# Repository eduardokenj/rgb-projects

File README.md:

Aqui nesse repositorio você encontrará os projeots relacionados ao RGB, como switchs para EURO SCART, bypass e adaptadores.
Caso queira produzir a placa recomendo esses dois sites abaixo ambos no exterior, mas que enviam para o Brasil

 SEEED FUSION: https://www.seeedstudio.com/fusion_pcb.html (envie o arquivo .zip incluso no diretorio do projeto);
	
 OSH PARK: https://oshpark.com/ (envie o arquivo .brd que se encontra no dietorio do projeto).
	
E boa parte dos compoenentes são encontrados já nacionalizados.

Os projetos nesse repositorio git são open hardware e feitos para a comunidade.

Caso queira doar via paypal só mandar o pagameto para eduardokenj@gmail.com
Ou via PicPay picpay.me/eduardo.asakura

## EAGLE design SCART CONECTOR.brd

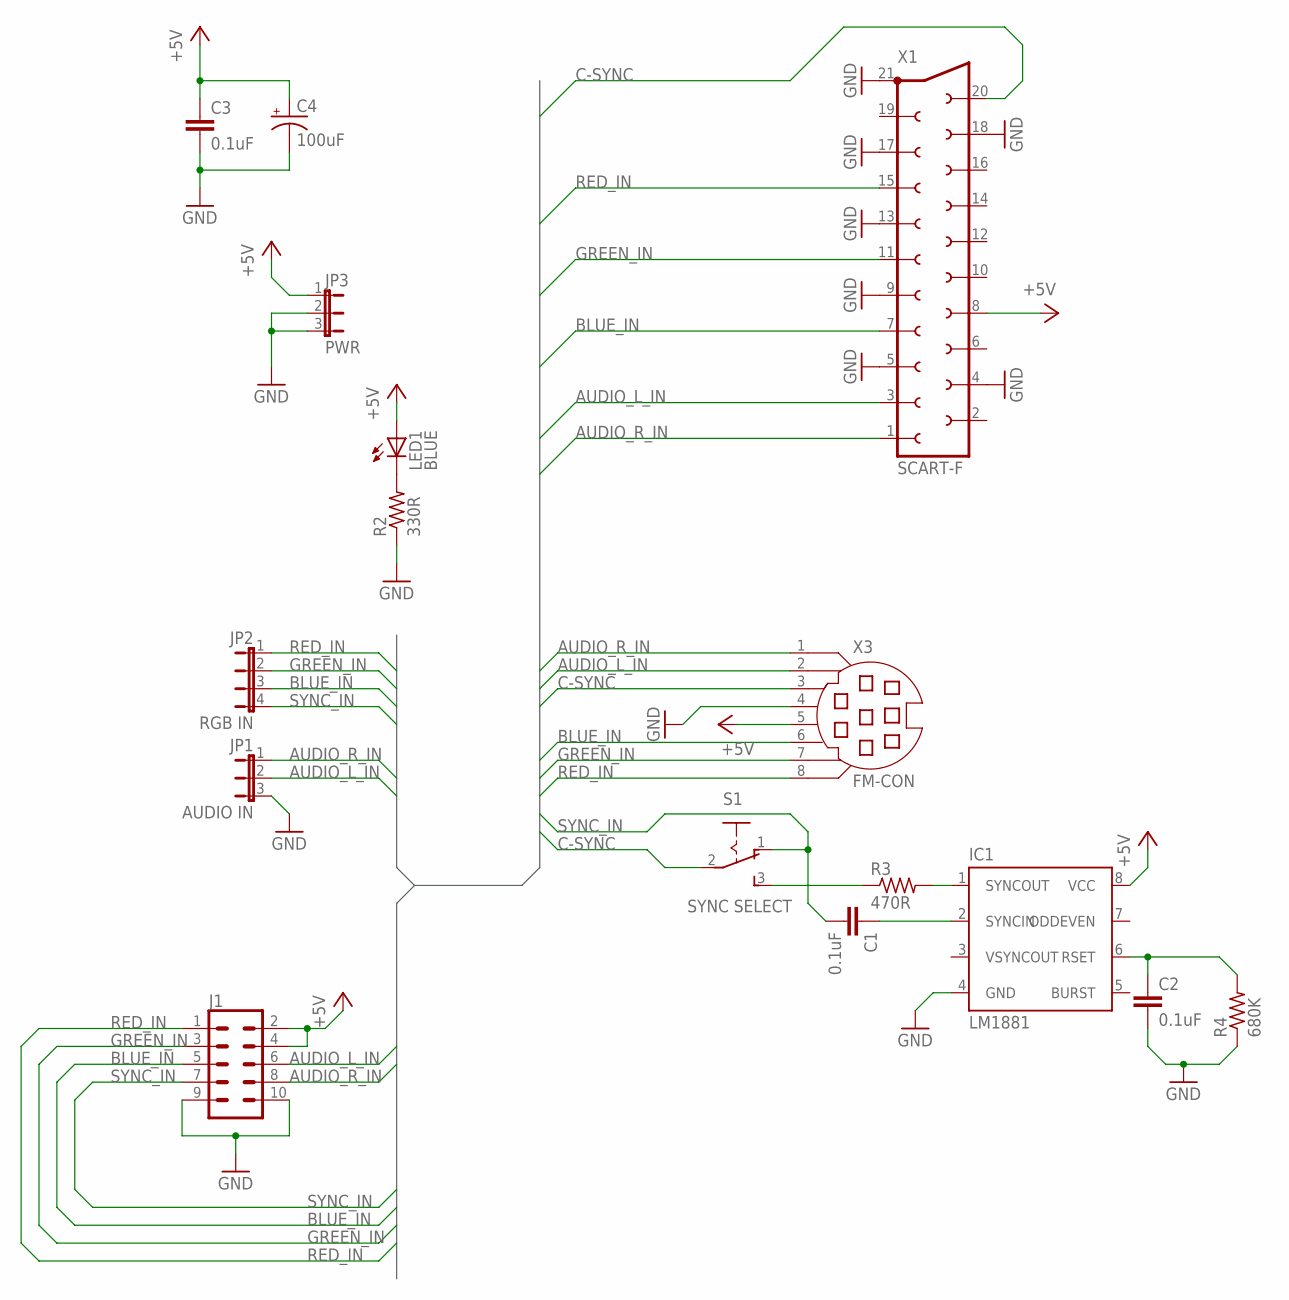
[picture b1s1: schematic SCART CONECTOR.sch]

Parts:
C1, C2, C3: 0.1uF; C7.5B3
C4: 100uF; E5-13
IC1: LM1881; DIL08
J1: CONN_05X2SHD-NS; 2X5-SHROUDED-NS
JP1: AUDIO IN; JP2
JP2: RGB IN; JP4
JP3: PWR; JP2
LED1: BLUE; LED5MM
R2: 330R; 0204/7
R3: 470R; 0204/7
R4: 680K; 0204/7
S1: SYNC SELECT; 255SB
X1: SCART-F
X3: FM-CON; MDIN08SS

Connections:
+5V: C3.1, C4.+, IC1.8 (VCC), J1.2, J1.4, JP3.1, LED1.A, X1.8, X3.5
AUDIO_L_IN: J1.6, JP1.2, X1.3, X3.2
AUDIO_R_IN: J1.8, JP1.1, X1.1, X3.1
BLUE_IN: J1.5, JP2.3, X1.7, X3.6
C-SYNC: S1.2, X1.20, X3.3
GND: C2.2, C3.2, C4.-, IC1.4 (GND), J1.9, J1.10, JP1.3, JP3.2, JP3.3, R2.1, R4.1, X1.4, X1.5, X1.9, X1.13, X1.17, X1.18, X1.21, X3.4
GREEN_IN: J1.3, JP2.2, X1.11, X3.7
unnamed: R3.1, S1.3 (S)
unnamed: IC1.1 (SYNCOUT), R3.2
unnamed: LED1.K (C), R2.2
unnamed: C1.1, IC1.2 (SYNCIN)
unnamed: C2.1, IC1.6 (RSET), R4.2
RED_IN: J1.1, JP2.1, X1.15, X3.8
SYNC_IN: C1.2, J1.7, JP2.4, S1.1 (O)

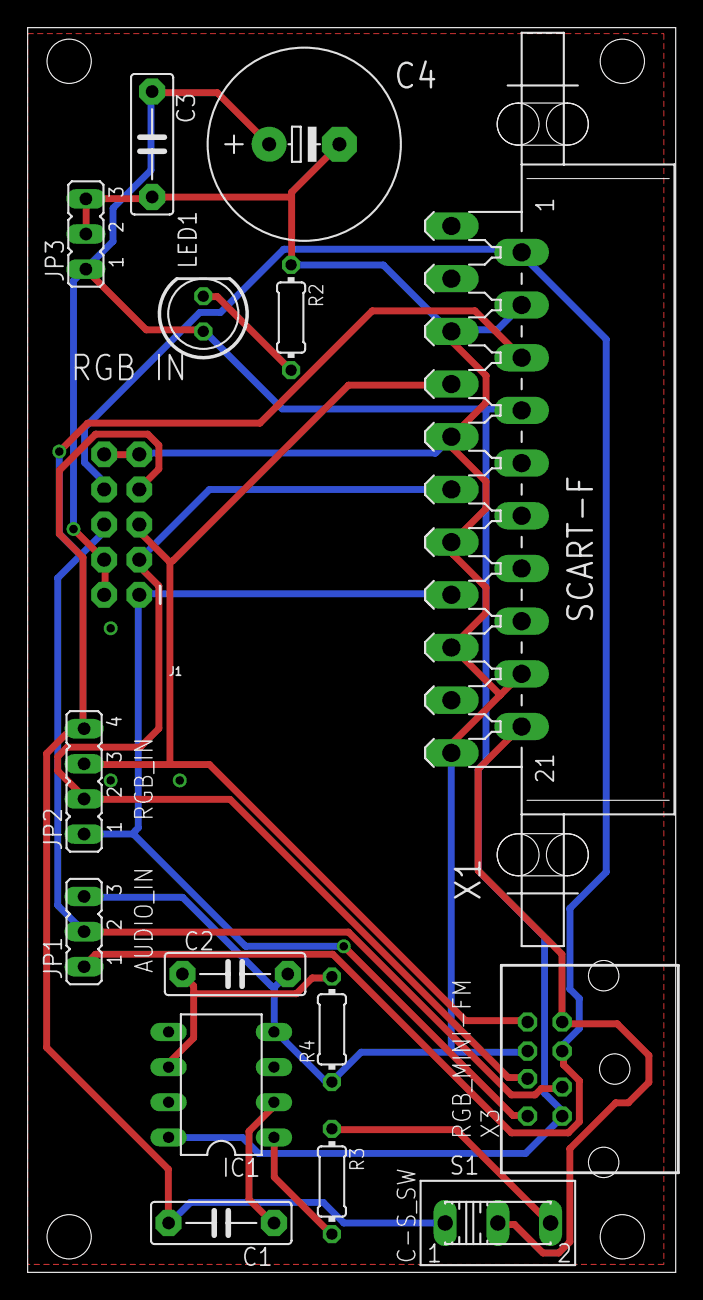
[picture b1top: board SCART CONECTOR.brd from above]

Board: 2 copper layers, 46.9 x 90.0 mm, 16 parts (0 on the bottom side), 14 nets.

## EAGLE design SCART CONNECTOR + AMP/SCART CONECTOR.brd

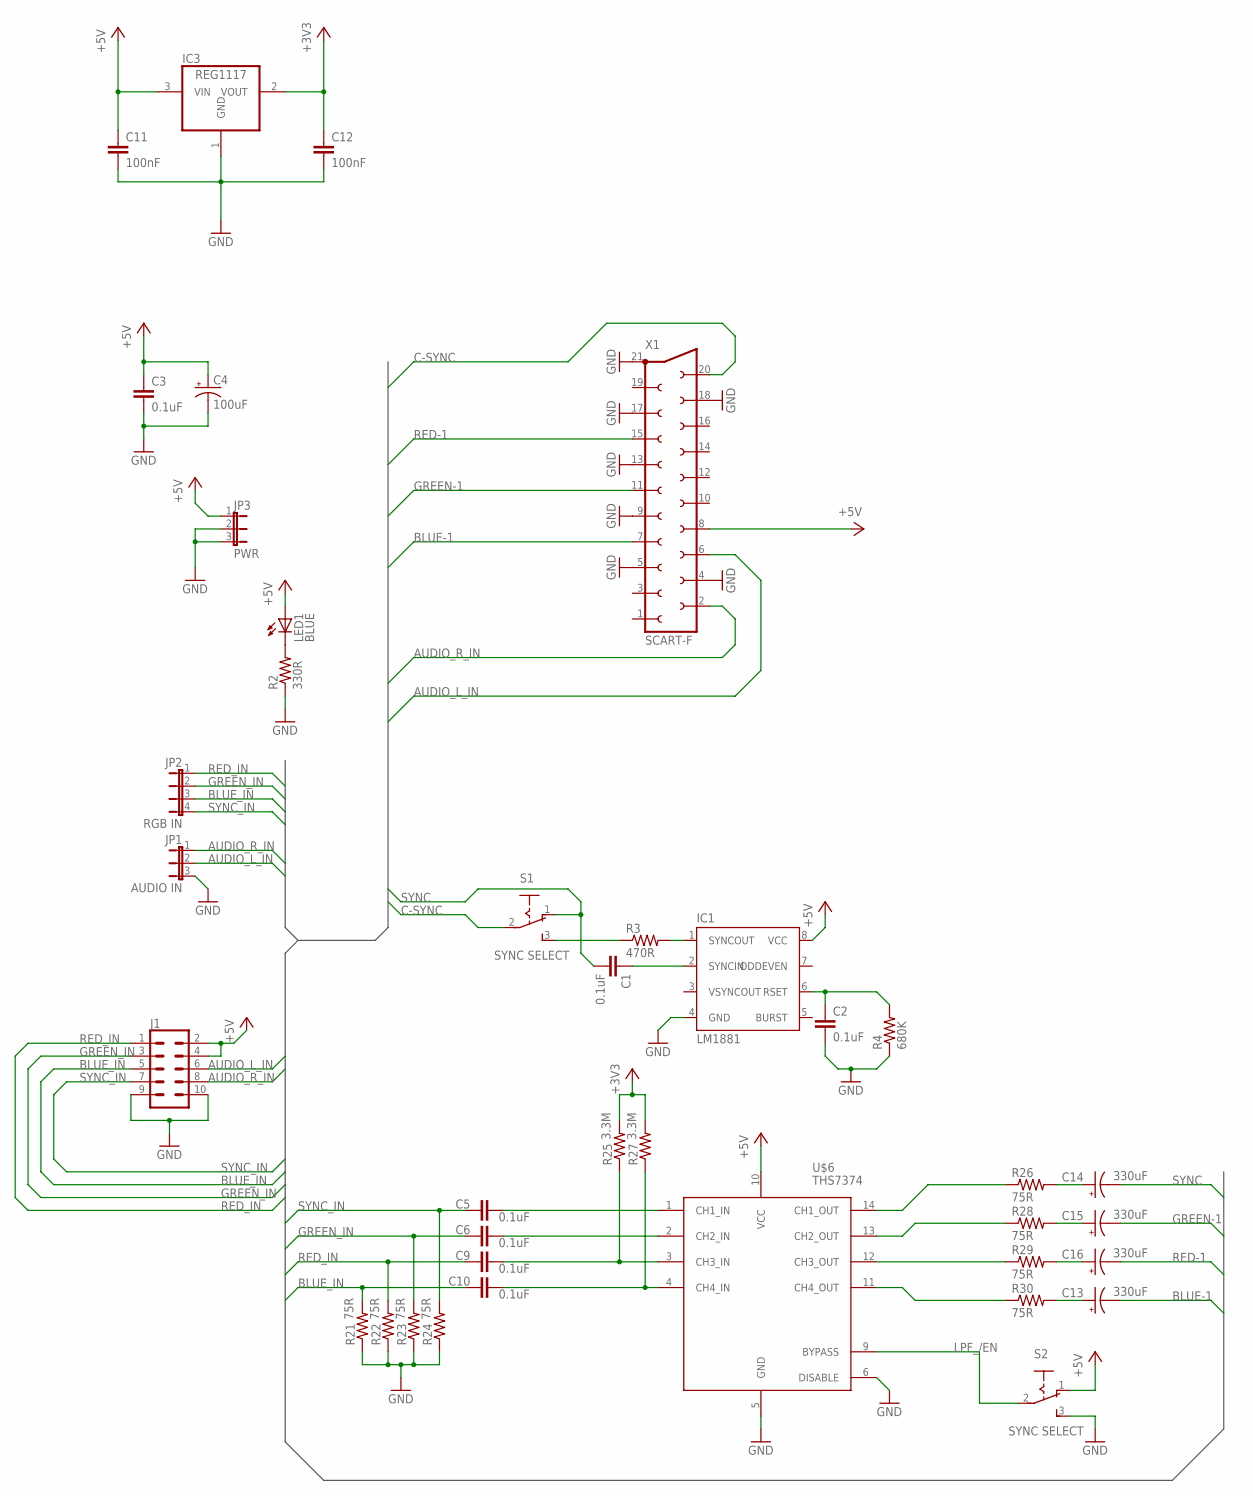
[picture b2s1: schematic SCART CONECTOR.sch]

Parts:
C1, C2, C3: 0.1uF; C7.5B3
C4: 100uF; E5-13
C5, C6, C9, C10: 0.1uF; C050-025X075
C11, C12: 100nF; C075-032X103
C13, C14, C15, C16: 330uF; D/7343-31W
IC1: LM1881; DIL08
IC3: REG1117; SOT223
J1: CONN_05X2SHD-NS; 2X5-SHROUDED-NS
JP1: AUDIO IN; JP2
JP2: RGB IN; JP4
JP3: PWR; JP2
LED1: BLUE; LED5MM
R2: 330R; 0204/7
R3: 470R; 0204/7
R4: 680K; 0204/7
R21, R22, R23, R24: 75R; 0204V
R25, R27: 3.3M; 0204/7
R26, R28, R29, R30: 75R; 0204/7
S1, S2: SYNC SELECT; 255SB
U$6: THS7374; TSSOP-14
X1: SCART-F

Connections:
+3V3: C12.1, IC3.2 (VOUT), R25.2, R27.2
+5V: C3.1, C4.+, C11.1, IC1.8 (VCC), IC3.3 (VIN), J1.2, J1.4, JP3.1, LED1.A, S2.1 (O), U$6.10 (VCC), X1.8
AUDIO_L_IN: J1.6, JP1.2, X1.6
AUDIO_R_IN: J1.8, JP1.1, X1.2
BLUE-1: C13.-, X1.7
BLUE_IN: C10.1, J1.5, JP2.3, R21.2
C-SYNC: S1.2, X1.20
GND: C2.2, C3.2, C4.-, C11.2, C12.2, IC1.4 (GND), IC3.1 (GND), J1.9, J1.10, JP1.3, JP3.2, JP3.3, R2.1, R4.1, R21.1, R22.1, R23.1, R24.1, S2.3 (S), U$6.5 (GND), U$6.6 (DISABLE), X1.4, X1.5, X1.9, X1.13, X1.17, X1.18, X1.21
GREEN-1: C15.-, X1.11
GREEN_IN: C6.1, J1.3, JP2.2, R23.2
LPF_/EN: S2.2, U$6.9 (BYPASS)
unnamed: R3.1, S1.3 (S)
unnamed: IC1.1 (SYNCOUT), R3.2
unnamed: LED1.K (C), R2.2
unnamed: C1.1, IC1.2 (SYNCIN)
unnamed: C2.1, IC1.6 (RSET), R4.2
unnamed: C6.2, U$6.2 (CH2_IN)
unnamed: C9.2, R25.1, U$6.3 (CH3_IN)
unnamed: C10.2, R27.1, U$6.4 (CH4_IN)
unnamed: C5.2, U$6.1 (CH1_IN)
unnamed: R26.1, U$6.14 (CH1_OUT)
unnamed: R28.1, U$6.13 (CH2_OUT)
unnamed: R29.1, U$6.12 (CH3_OUT)
unnamed: R30.1, U$6.11 (CH4_OUT)
unnamed: C13.+, R30.2
unnamed: C16.+, R29.2
unnamed: C15.+, R28.2
unnamed: C14.+, R26.2
RED-1: C16.-, X1.15
RED_IN: C9.1, J1.1, JP2.1, R22.2
SYNC: C1.2, C14.-, S1.1 (O)
SYNC_IN: C5.1, J1.7, JP2.4, R24.2

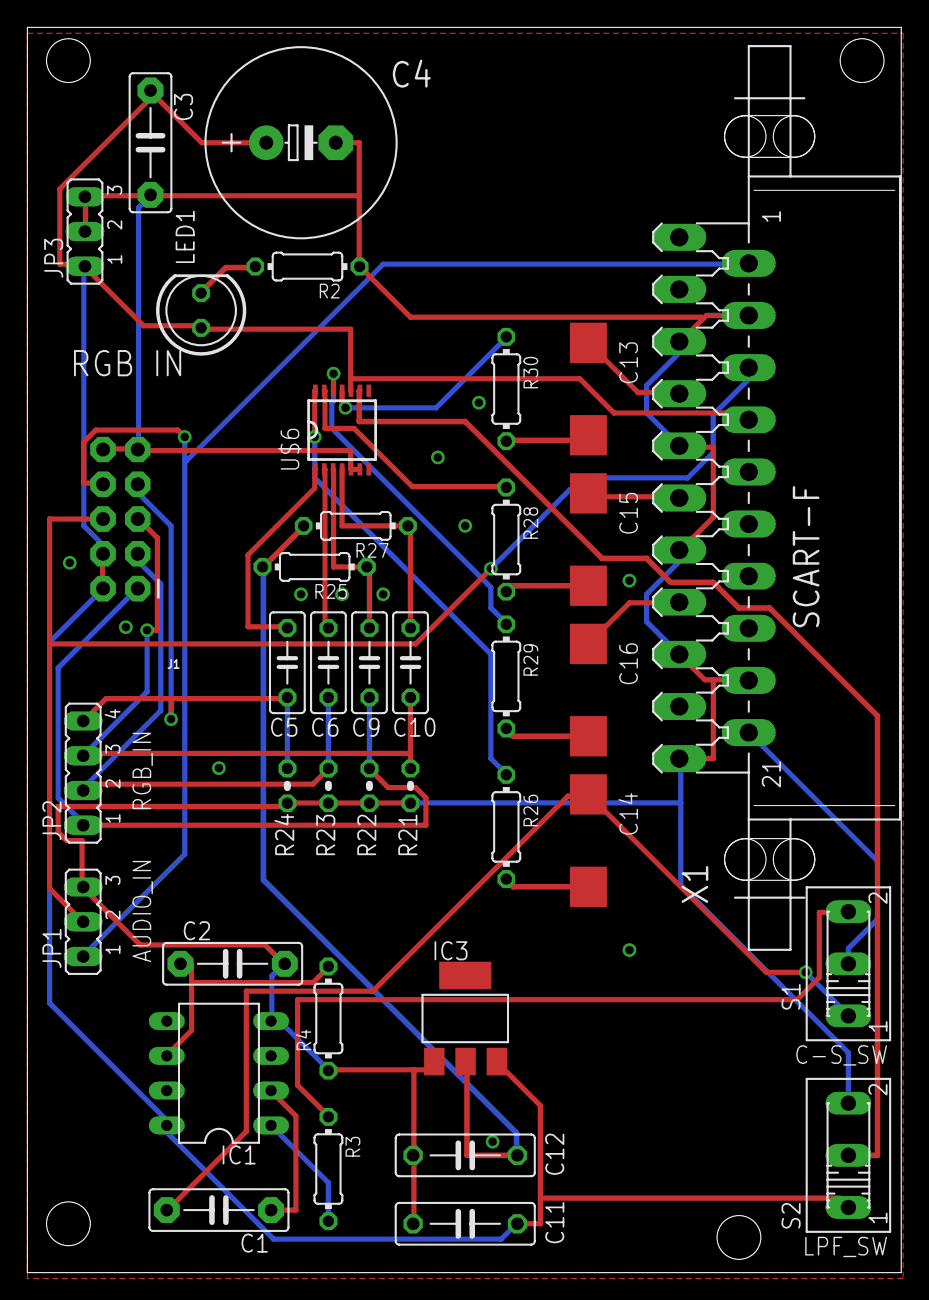
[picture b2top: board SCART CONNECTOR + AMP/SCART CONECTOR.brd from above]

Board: 2 copper layers, 63.9 x 91.0 mm, 38 parts (0 on the bottom side), 32 nets.

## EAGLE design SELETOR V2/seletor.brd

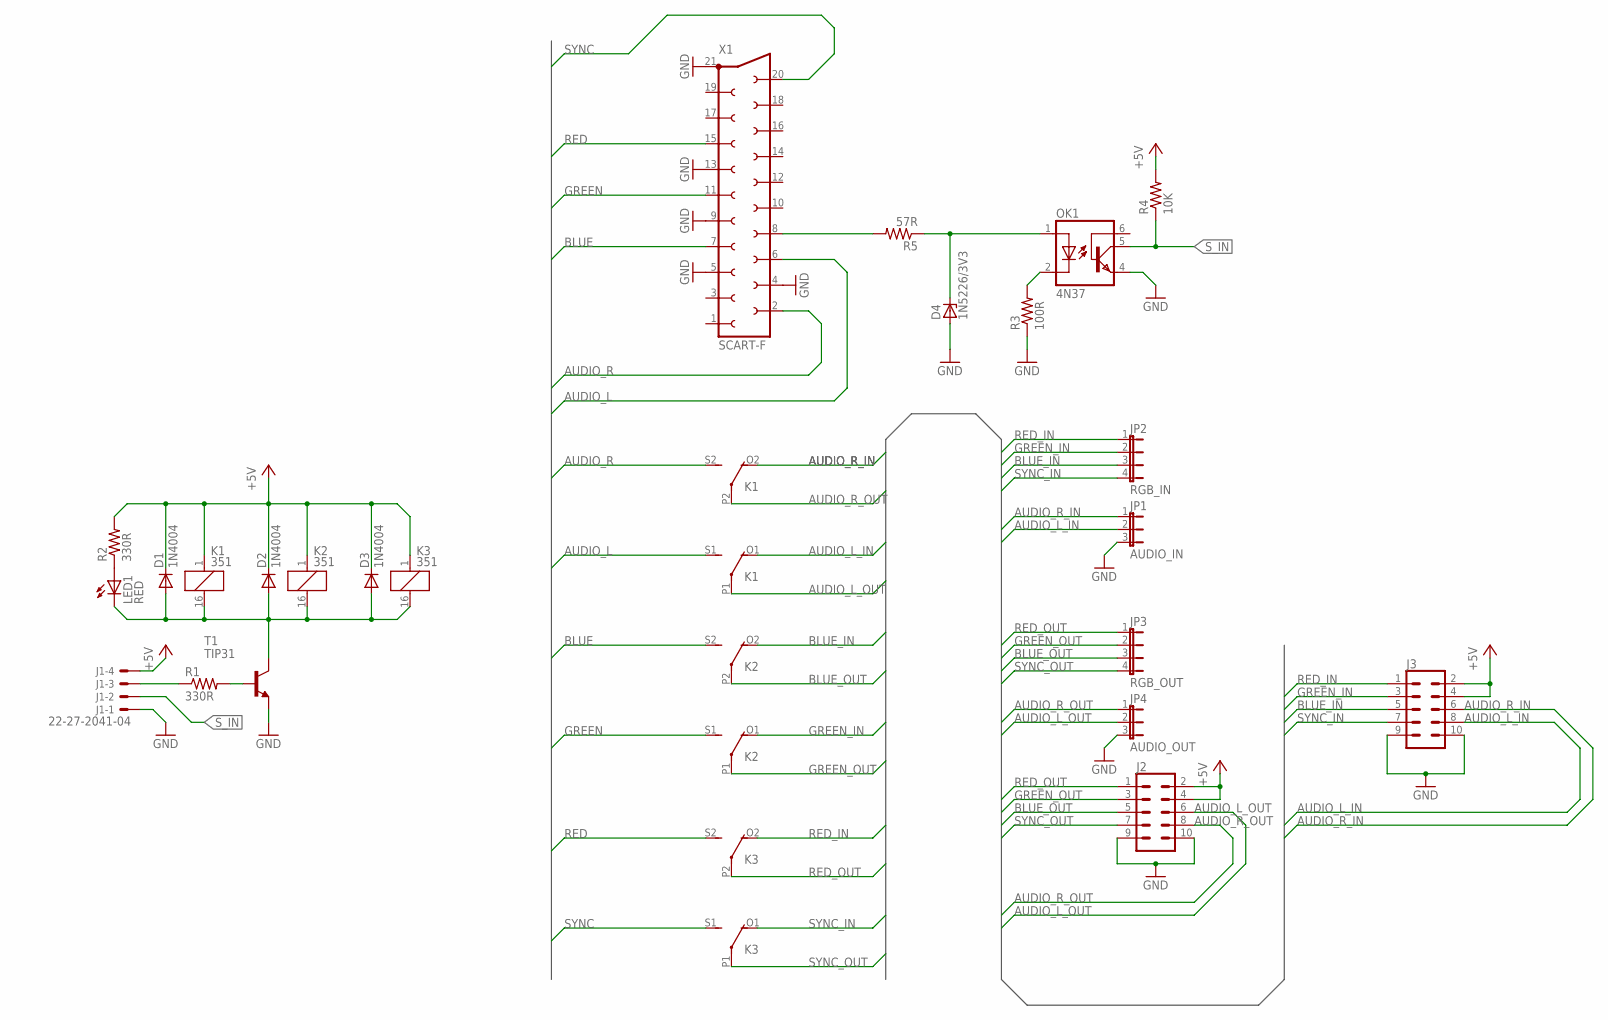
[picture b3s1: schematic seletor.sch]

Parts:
D1, D2, D3: 1N4004; DO41-10
D4: 1N5226/3V3; DO34Z7
J1: 22-27-2041-04; 6410-04
J2, J3: CONN_05X2SHD-NS; 2X5-SHROUDED-NS
JP1: AUDIO_IN; JP2
JP2: RGB_IN; JP4
JP3: RGB_OUT; JP4
JP4: AUDIO_OUT; JP2
K1, K2, K3: 351
LED1: RED; LED5MM
OK1: 4N37; DIL06
R1, R2: 330R; 0204/7
R3: 100R; 0204/7
R4: 10K; 0204/7
R5: 57R; 0204/7
T1: TIP31; TO220
X1: SCART-F

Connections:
+5V: D1.C, D2.C, D3.C, J1.4, J2.2, J2.4, J3.2, J3.4, K1.1, K2.1, K3.1, R2.2, R4.2
AUDIO_L: K1.S1 (S), X1.6
AUDIO_L_IN: J3.8, JP1.2, K1.O1 (O)
AUDIO_L_OUT: J2.6, JP4.2, K1.P1
AUDIO_R: K1.S2 (S), X1.2
AUDIO_R_IN: J3.6, JP1.1, K1.O2 (O)
AUDIO_R_OUT: J2.8, JP4.1, K1.P2
BLUE: K2.S2 (S), X1.7
BLUE_IN: J3.5, JP2.3, K2.O2 (O)
BLUE_OUT: J2.5, JP3.3, K2.P2
GND: D4.A, J1.1, J2.9, J2.10, J3.9, J3.10, JP1.3, JP4.3, OK1.4 (EMI), R3.1, T1.3 (E), X1.4, X1.5, X1.9, X1.13, X1.21
GREEN: K2.S1 (S), X1.11
GREEN_IN: J3.3, JP2.2, K2.O1 (O)
GREEN_OUT: J2.3, JP3.2, K2.P1
unnamed: J1.3, R1.1
unnamed: D1.A, D2.A, D3.A, K1.16 (2), K2.16 (2), K3.16 (2), LED1.K (C), T1.2 (C)
unnamed: LED1.A, R2.1
unnamed: D4.C, OK1.1 (A), R5.1
unnamed: OK1.2 (C), R3.2
unnamed: R5.2, X1.8
unnamed: R1.2, T1.1 (B)
RED: K3.S2 (S), X1.15
RED_IN: J3.1, JP2.1, K3.O2 (O)
RED_OUT: J2.1, JP3.1, K3.P2
SYNC: K3.S1 (S), X1.20
SYNC_IN: J3.7, JP2.4, K3.O1 (O)
SYNC_OUT: J2.7, JP3.4, K3.P1
S_IN: J1.2, OK1.5 (COL), R4.1

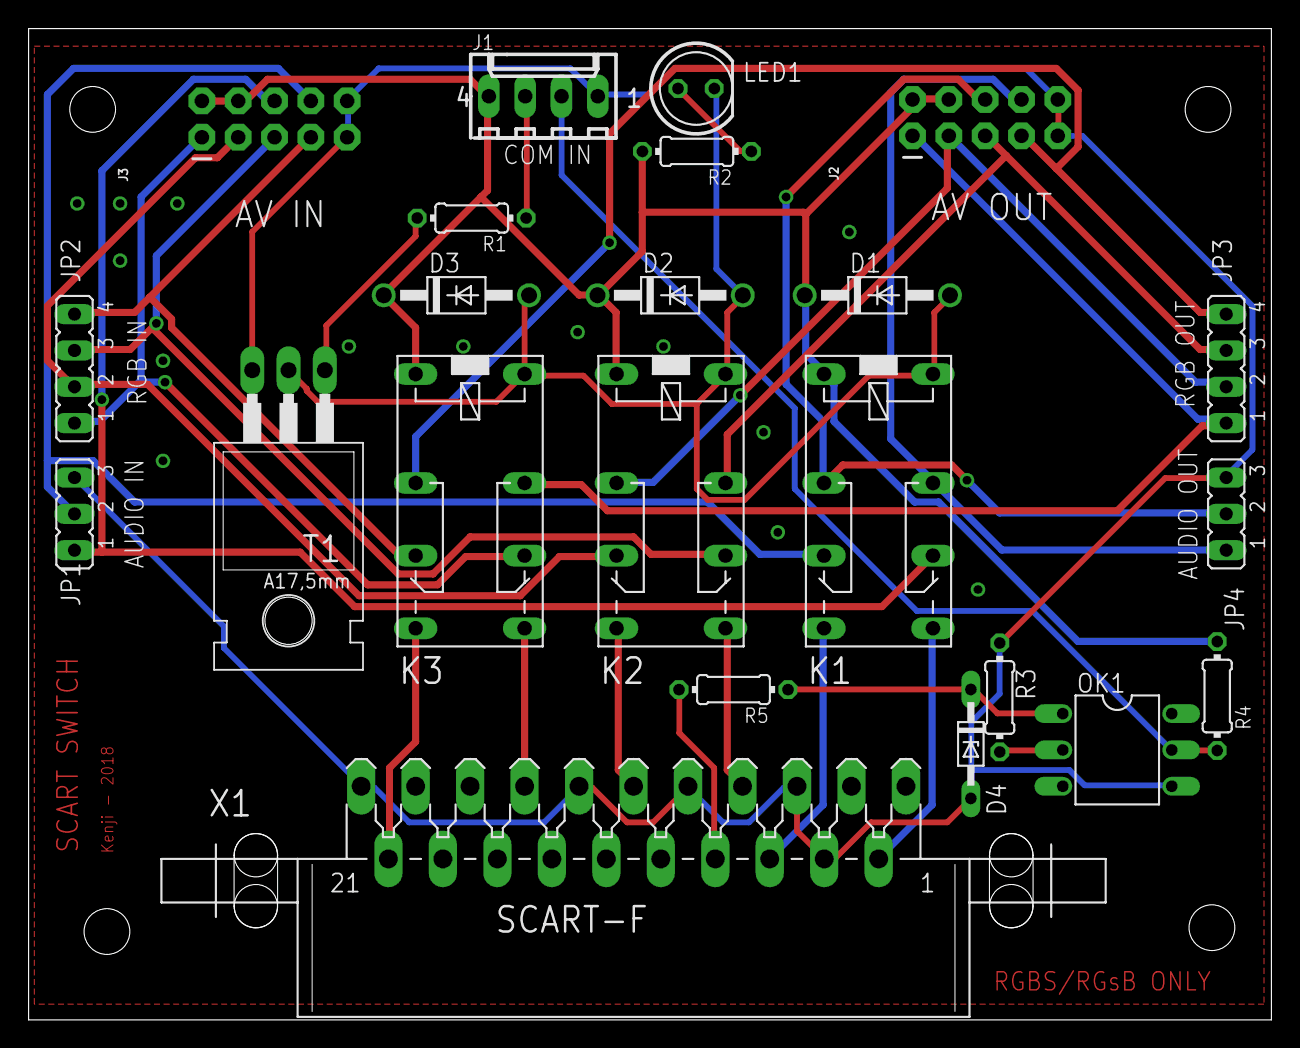
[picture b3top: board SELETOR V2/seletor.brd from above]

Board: 2 copper layers, 86.9 x 69.3 mm, 23 parts (0 on the bottom side), 28 nets.

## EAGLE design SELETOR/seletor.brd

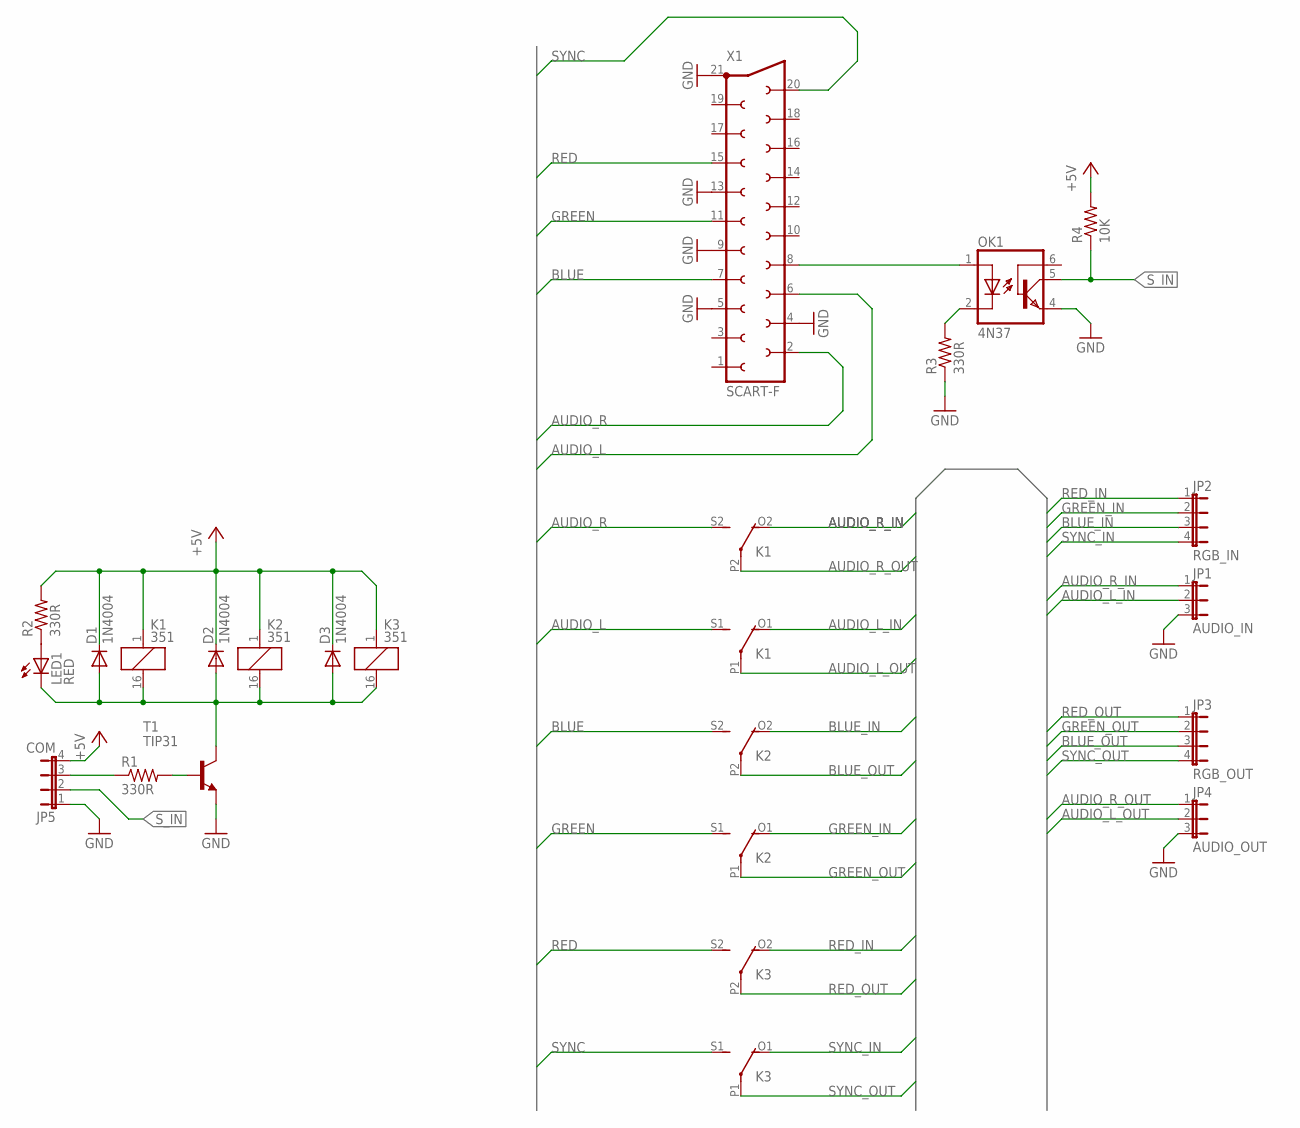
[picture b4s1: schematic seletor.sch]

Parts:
D1, D2, D3: 1N4004; DO41-10
JP1: AUDIO_IN; JP2
JP2: RGB_IN; JP4
JP3: RGB_OUT; JP4
JP4: AUDIO_OUT; JP2
JP5: COM; JP4
K1, K2, K3: 351
LED1: RED; LED5MM
OK1: 4N37; DIL06
R1: 330R; 0204/7
R2, R3: 330R; 0204V
R4: 10K; 0204V
T1: TIP31; TO220
X1: SCART-F

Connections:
+5V: D1.C, D2.C, D3.C, JP5.4, K1.1, K2.1, K3.1, R2.2, R4.2
AUDIO_L: K1.S1 (S), X1.6
AUDIO_L_IN: JP1.2, K1.O1 (O)
AUDIO_L_OUT: JP4.2, K1.P1
AUDIO_R: K1.S2 (S), X1.2
AUDIO_R_IN: JP1.1, K1.O2 (O)
AUDIO_R_OUT: JP4.1, K1.P2
BLUE: K2.S2 (S), X1.7
BLUE_IN: JP2.3, K2.O2 (O)
BLUE_OUT: JP3.3, K2.P2
GND: JP1.3, JP4.3, JP5.1, OK1.4 (EMI), R3.1, T1.3 (E), X1.4, X1.5, X1.9, X1.13, X1.21
GREEN: K2.S1 (S), X1.11
GREEN_IN: JP2.2, K2.O1 (O)
GREEN_OUT: JP3.2, K2.P1
unnamed: JP5.3, R1.1
unnamed: D1.A, D2.A, D3.A, K1.16 (2), K2.16 (2), K3.16 (2), LED1.K (C), T1.2 (C)
unnamed: LED1.A, R2.1
unnamed: OK1.1 (A), X1.8
unnamed: OK1.2 (C), R3.2
unnamed: R1.2, T1.1 (B)
RED: K3.S2 (S), X1.15
RED_IN: JP2.1, K3.O2 (O)
RED_OUT: JP3.1, K3.P2
SYNC: K3.S1 (S), X1.20
SYNC_IN: JP2.4, K3.O1 (O)
SYNC_OUT: JP3.4, K3.P1
S_IN: JP5.2, OK1.5 (COL), R4.1

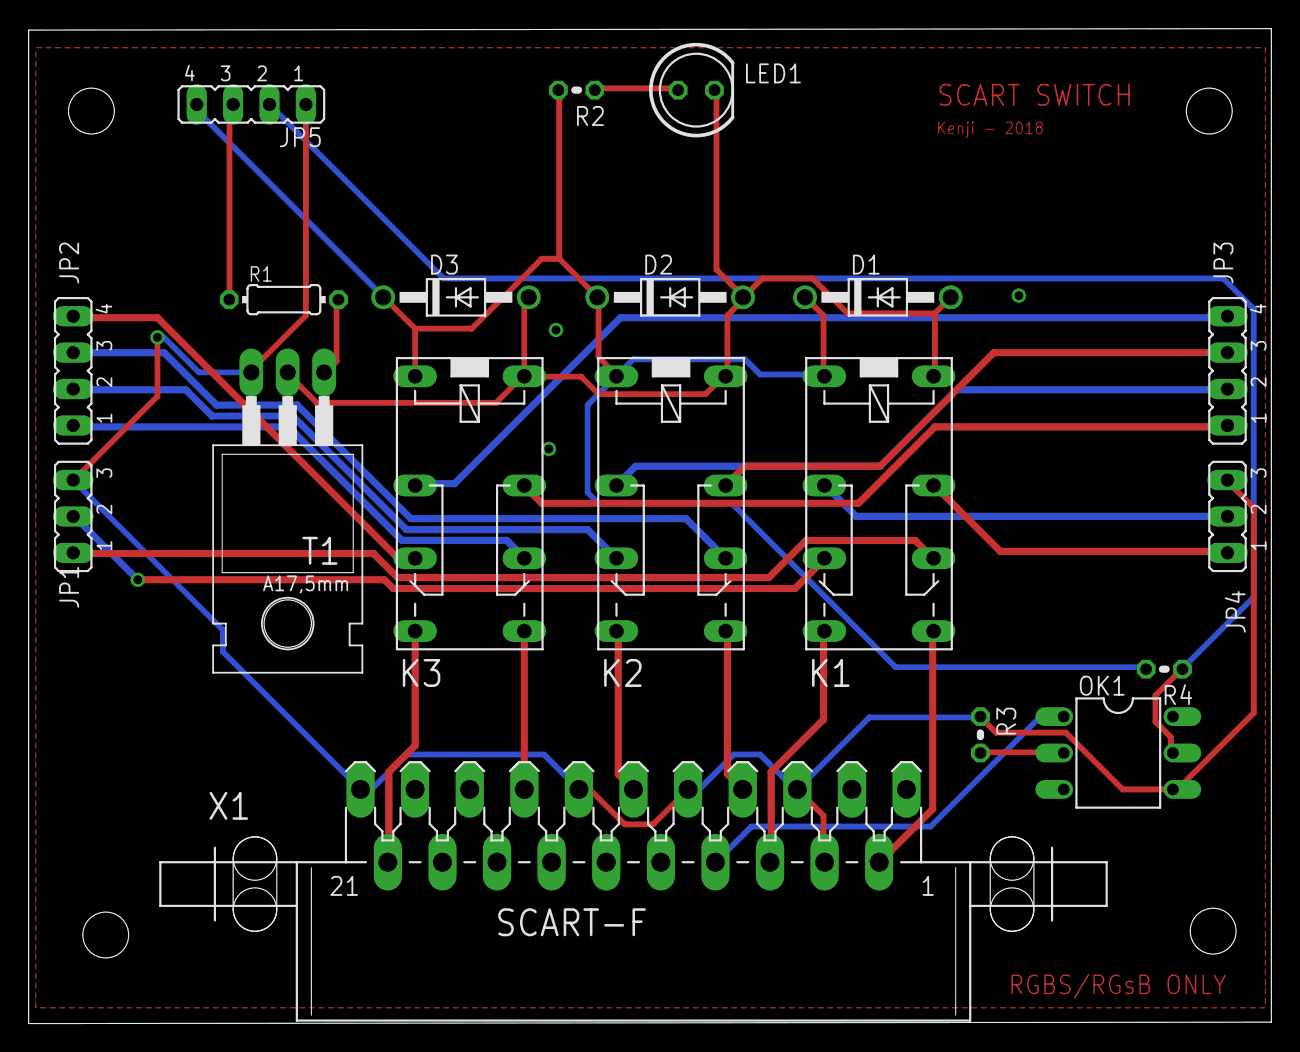
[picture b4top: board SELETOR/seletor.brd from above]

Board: 2 copper layers, 86.7 x 69.4 mm, 19 parts (0 on the bottom side), 27 nets.

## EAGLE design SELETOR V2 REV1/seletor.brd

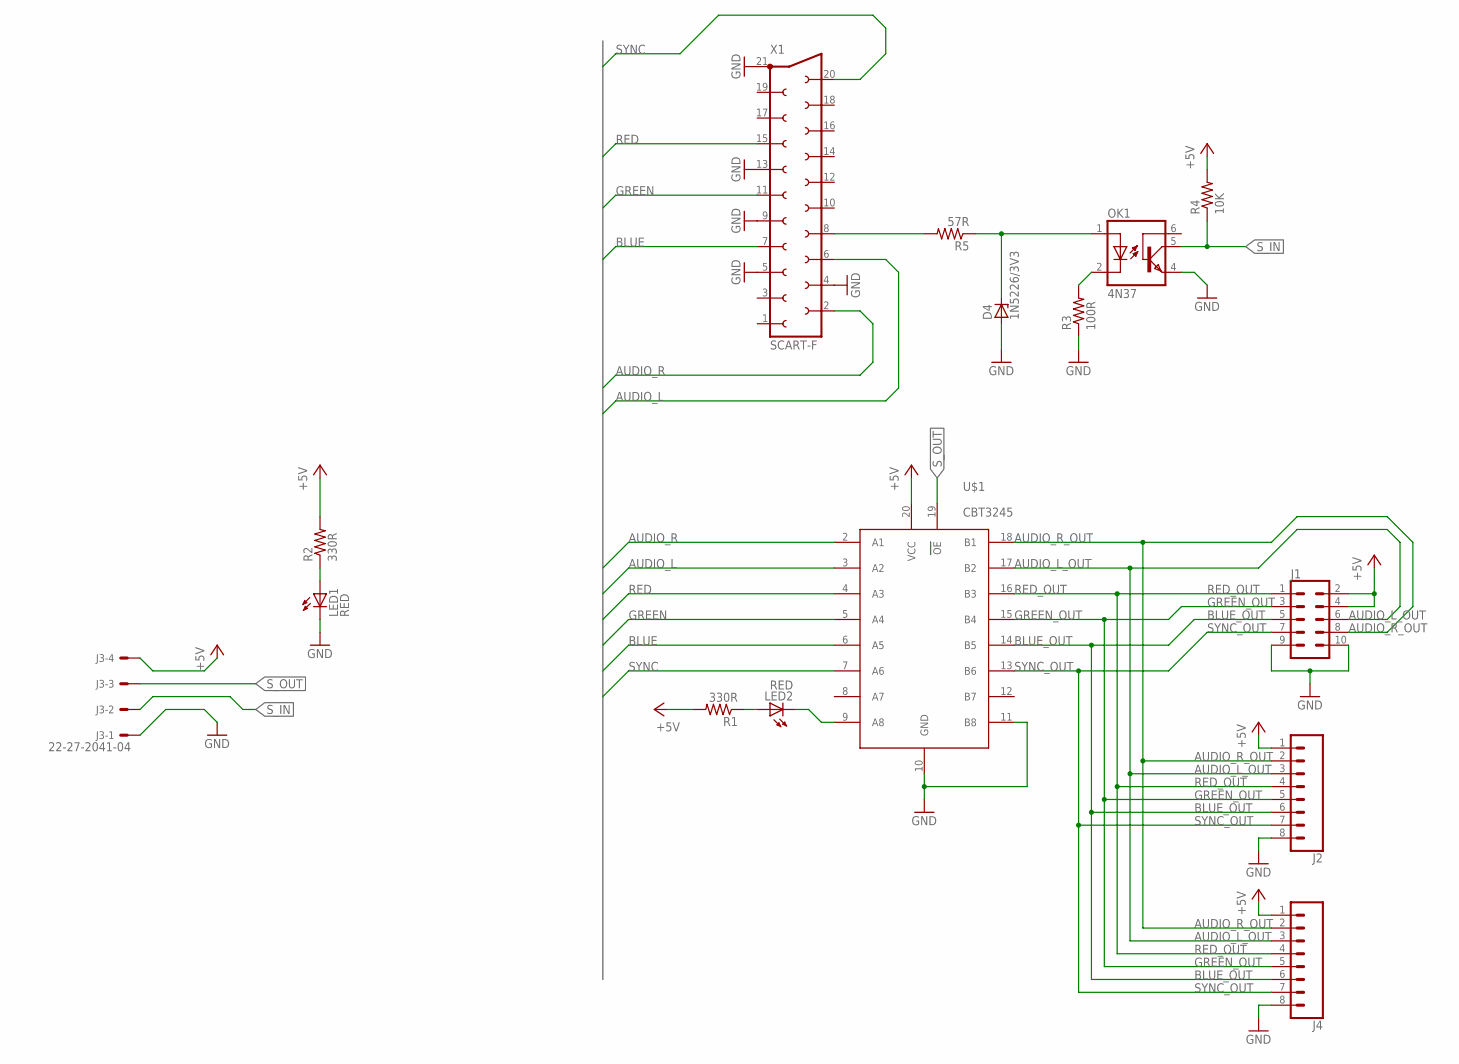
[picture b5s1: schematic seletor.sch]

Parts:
D4: 1N5226/3V3; DO34Z7
J1: CONN_05X2SHD; 2X5-SHROUDED
J2, J4: CONN_08"; 1X08
J3: 22-27-2041-04; 6410-04
LED1, LED2: RED; LED5MM
OK1: 4N37; DIL06
R1, R2: 330R; 0204V
R3: 100R; 0204V
R4: 10K; 0204V
R5: 57R; 0204/7
U$1: CBT3245; SO20
X1: SCART-F

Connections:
+5V: J1.2, J1.4, J2.1, J3.4, J4.1, R1.2, R2.2, R4.2, U$1.20 (VCC)
AUDIO_L: U$1.3 (A2), X1.6
AUDIO_L_OUT: J1.6, J2.3, J4.3, U$1.17 (B2)
AUDIO_R: U$1.2 (A1), X1.2
AUDIO_R_OUT: J1.8, J2.2, J4.2, U$1.18 (B1)
BLUE: U$1.6 (A5), X1.7
BLUE_OUT: J1.5, J2.6, J4.6, U$1.14 (B5)
GND: D4.A, J1.9, J1.10, J2.8, J3.1, J4.8, LED1.K (C), OK1.4 (EMI), R3.1, U$1.10 (GND), U$1.11 (B8), X1.4, X1.5, X1.9, X1.13, X1.21
GREEN: U$1.5 (A4), X1.11
GREEN_OUT: J1.3, J2.5, J4.5, U$1.15 (B4)
unnamed: LED1.A, R2.1
unnamed: D4.C, OK1.1 (A), R5.1
unnamed: OK1.2 (C), R3.2
unnamed: R5.2, X1.8
unnamed: LED2.A, R1.1
unnamed: LED2.K (C), U$1.9 (A8)
RED: U$1.4 (A3), X1.15
RED_OUT: J1.1, J2.4, J4.4, U$1.16 (B3)
SYNC: U$1.7 (A6), X1.20
SYNC_OUT: J1.7, J2.7, J4.7, U$1.13 (B6)
S_IN: J3.2, OK1.5 (COL), R4.1
S_OUT: J3.3, U$1.19 (OE)

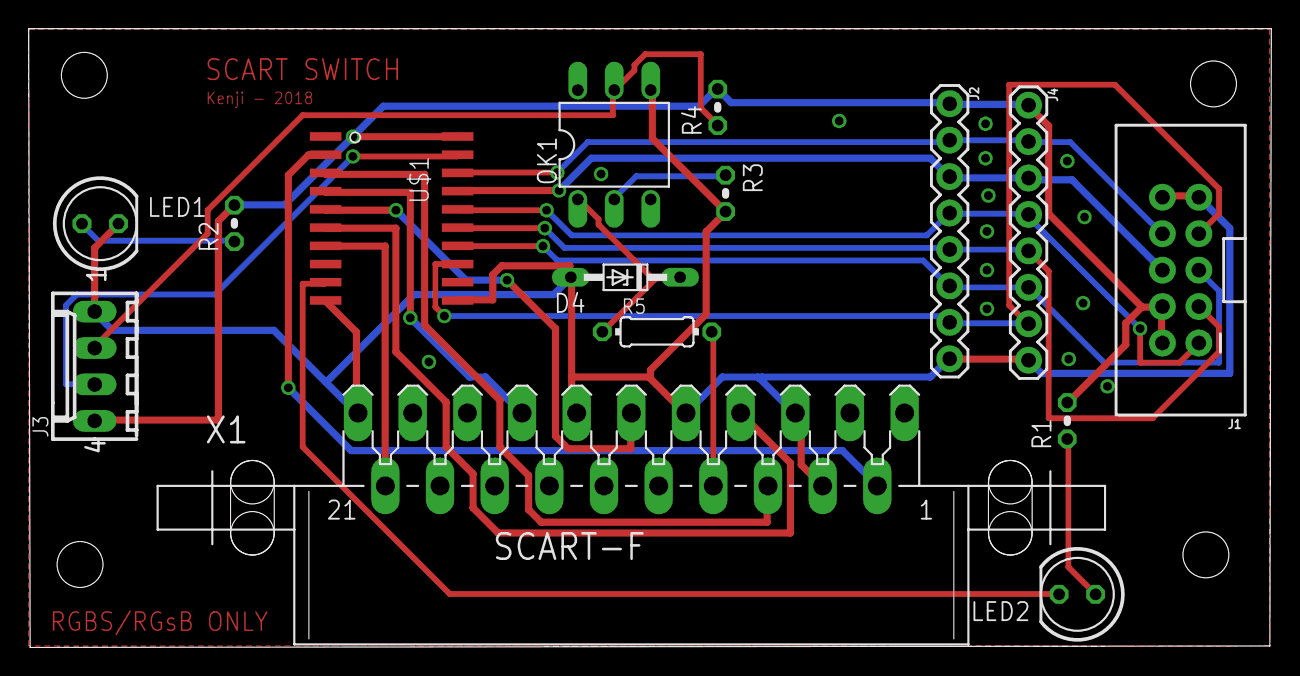
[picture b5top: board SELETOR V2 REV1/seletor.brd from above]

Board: 2 copper layers, 86.6 x 43.1 mm, 15 parts (0 on the bottom side), 22 nets.

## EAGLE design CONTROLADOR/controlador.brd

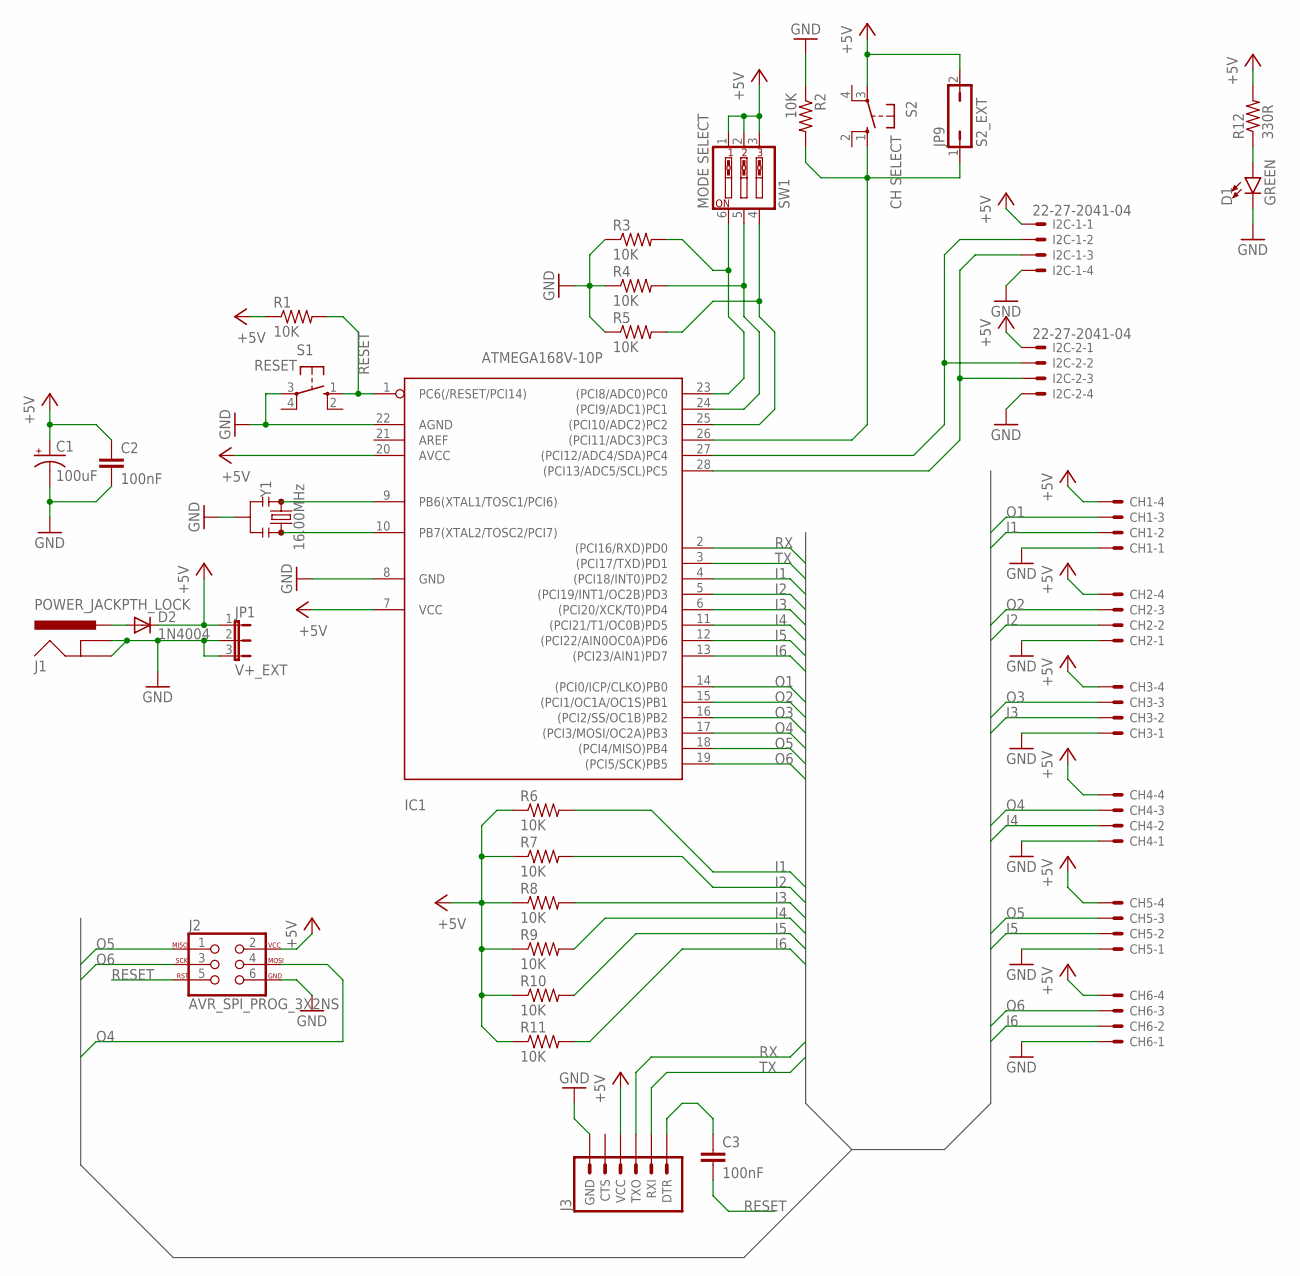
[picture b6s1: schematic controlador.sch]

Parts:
C1: 100uF; E2,5-7
C2, C3: 100nF; C075-032X103
CH1, CH2, CH3, CH4, CH5, CH6: 22-27-2041-04; 6410-04
D1: GREEN; LED_5MM
D2: 1N4004; DO41-10
I2C-1, I2C-2: 22-27-2041-04; 6410-04
IC1: ATMEGA168V-10P; DIL28-3
J1: POWER_JACKPTH_LOCK; POWER_JACK_PTH_LOCK
J2: AVR_SPI_PROG_3X2NS; 2X3-NS
J3: 6_PIN_SERIAL_TARGETSILK; 6_PIN_SERIAL_TARGET_SIDE_W_SILK
JP1: V+_EXT; JP2
JP9: S2_EXT; JP1
R1, R2, R3, R4, R5, R6, R7, R8, R9, R10, R11: 10K; 0204/7
R12: 330R; 0204/7
S1: RESET; B3F-10XX
S2: CH SELECT; B3F-10XX
SW1: MODE SELECT; EDG-03
Y1: 16.00MHz; RESONATOR-PTH-7.6X3.8

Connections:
+5V: C1.+, C2.1, CH1.4, CH2.4, CH3.4, CH4.4, CH5.4, CH6.4, D2.C, I2C-1.1, I2C-2.1, IC1.7 (VCC), IC1.20 (AVCC), J2.2, J3.P$4 (VCC), JP1.1, JP9.2, R1.1, R6.1, R7.1, R8.1, R9.1, R10.1, R11.1, R12.2, S2.3, SW1.1, SW1.2, SW1.3
GND: C1.-, C2.2, CH1.1, CH2.1, CH3.1, CH4.1, CH5.1, CH6.1, D1.K (C), I2C-1.4, I2C-2.4, IC1.8 (GND), IC1.22 (AGND), J1.GND, J1.GNDBREAK, J2.6, J3.P$6 (GND), JP1.2, JP1.3, R2.1, R3.1, R4.1, R5.1, S1.3, Y1.2
I1: CH1.2, IC1.4 ((PCI18/INT0)PD2), R6.2
I2: CH2.2, IC1.5 ((PCI19/INT1/OC2B)PD3), R7.2
I3: CH3.2, IC1.6 ((PCI20/XCK/T0)PD4), R8.2
I4: CH4.2, IC1.11 ((PCI21/T1/OC0B)PD5), R9.2
I5: CH5.2, IC1.12 ((PCI22/AIN0OC0A)PD6), R10.2
I6: CH6.2, IC1.13 ((PCI23/AIN1)PD7), R11.2
unnamed: IC1.9 (PB6(XTAL1/TOSC1/PCI6)), Y1.1
unnamed: IC1.10 (PB7(XTAL2/TOSC2/PCI7)), Y1.3
unnamed: D1.A, R12.1
unnamed: I2C-1.2, I2C-2.2, IC1.27 ((PCI12/ADC4/SDA)PC4)
unnamed: I2C-1.3, I2C-2.3, IC1.28 ((PCI13/ADC5/SCL)PC5)
unnamed: IC1.26 ((PCI11/ADC3)PC3), JP9.1, R2.2, S2.1 (S)
unnamed: C3.1, J3.P$1 (DTR)
unnamed: D2.A, J1.PWR
unnamed: IC1.23 ((PCI8/ADC0)PC0), R3.2, SW1.6
unnamed: IC1.24 ((PCI9/ADC1)PC1), R4.2, SW1.5
unnamed: IC1.25 ((PCI10/ADC2)PC2), R5.2, SW1.4
O1: CH1.3, IC1.14 ((PCI0/ICP/CLKO)PB0)
O2: CH2.3, IC1.15 ((PCI1/OC1A/OC1S)PB1)
O3: CH3.3, IC1.16 ((PCI2/SS/OC1B)PB2)
O4: CH4.3, IC1.17 ((PCI3/MOSI/OC2A)PB3), J2.4
O5: CH5.3, IC1.18 ((PCI4/MISO)PB4), J2.1
O6: CH6.3, IC1.19 ((PCI5/SCK)PB5), J2.3
RESET: C3.2, IC1.1 (PC6(/RESET/PCI14)), J2.5, R1.2, S1.1 (S)
RX: IC1.2 ((PCI16/RXD)PD0), J3.P$2 (TXO)
TX: IC1.3 ((PCI17/TXD)PD1), J3.P$3 (RXI)

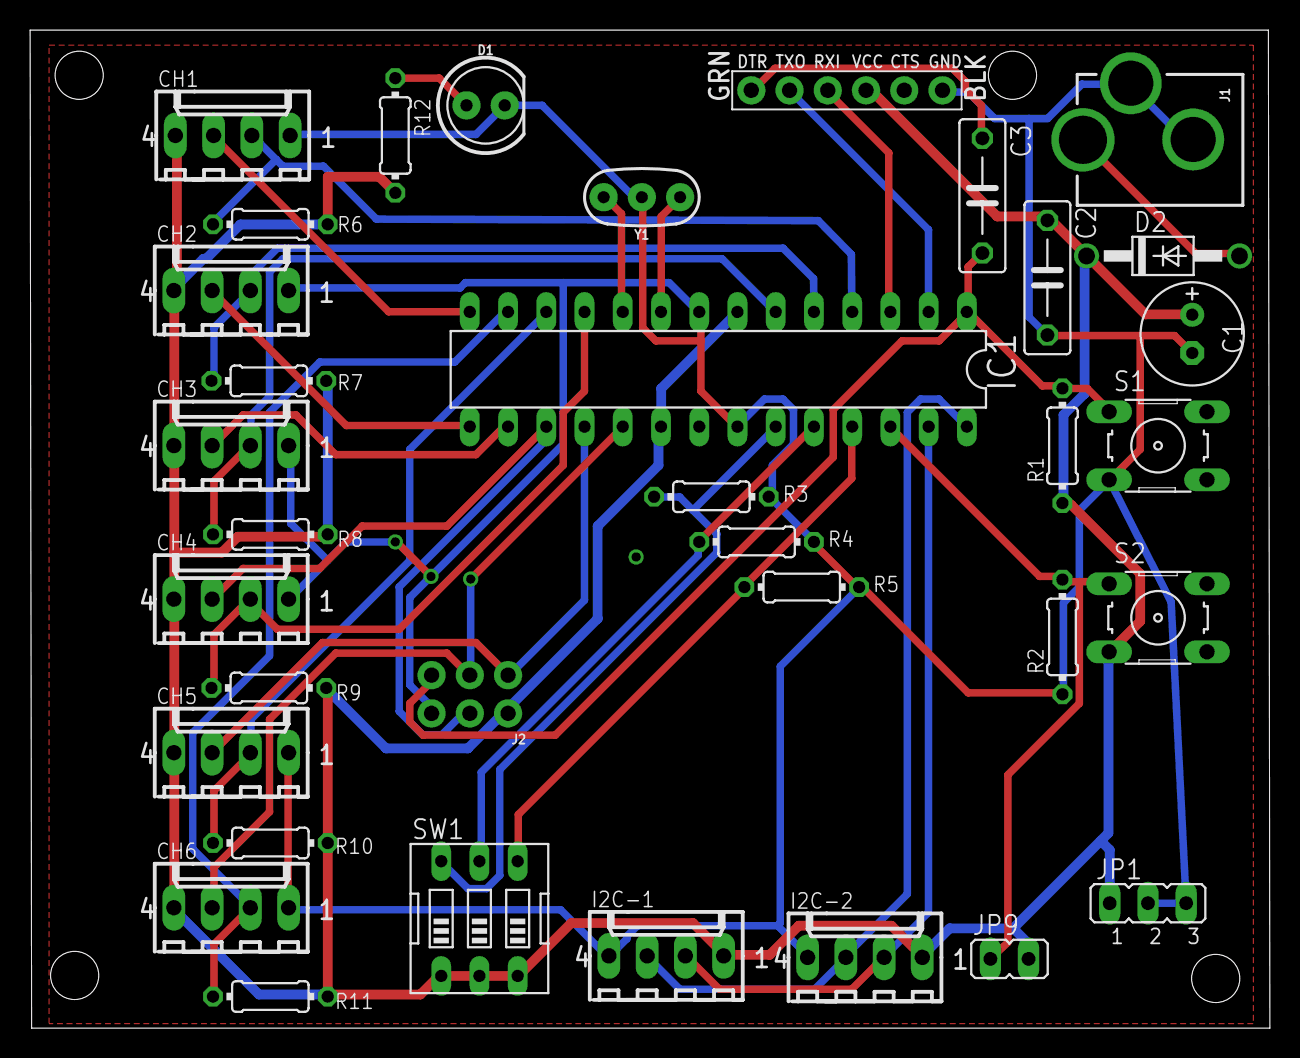
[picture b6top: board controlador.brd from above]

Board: 2 copper layers, 82.4 x 66.3 mm, 35 parts (0 on the bottom side), 28 nets.

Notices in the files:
parts and their libraries:
SparkFun-Connectors: Licensing: Creative Commons ShareAlike 4.0 International - https://creativecommons.org/licenses/by-sa/4.0
